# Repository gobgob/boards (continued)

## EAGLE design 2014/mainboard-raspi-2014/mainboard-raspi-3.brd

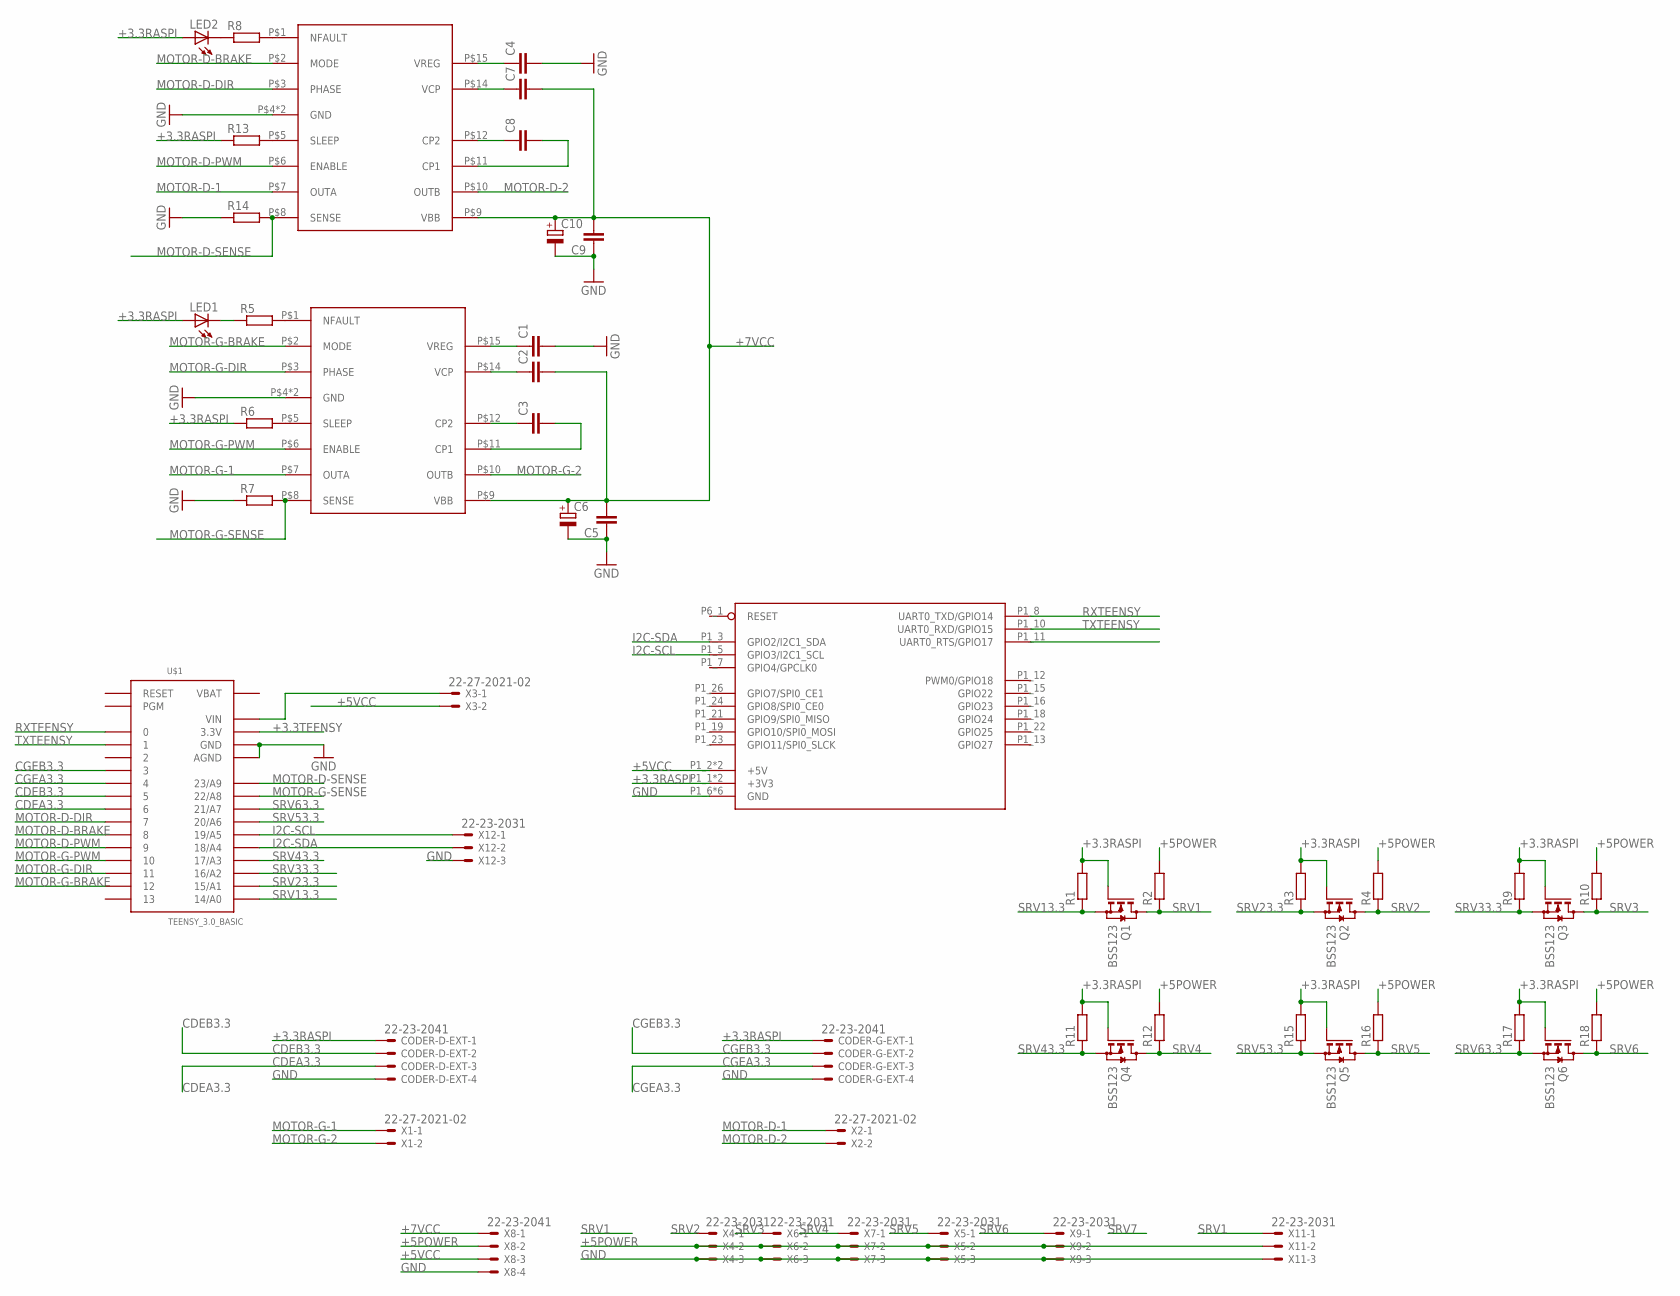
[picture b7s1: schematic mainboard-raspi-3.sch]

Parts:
C1, C2, C3, C4, C5, C7, C8, C9: C-EUC0805K; C0805K
C6, C10: CPOL-EUE3.5-8; E3,5-8
CODER-D-EXT: 22-23-2041
CODER-G-EXT: 22-23-2041
LED1, LED2: LED3MM
Q1, Q2, Q3, Q4, Q5, Q6: BSS123; SOT23
R1, R2, R3, R4, R9, R10, R11, R12, R15, R16, R17, R18: R-EU_R0603; R0603
R5, R8: R-EU_0204/7; 0204/7
R6, R7, R13, R14: R-EU_0204/5; 0204/5
U$1: TEENSY_3.0_BASIC
U$2: RPI-B-V2SHIELD; RPI-B-V2-SHIELD
U$3, U$4: A3950-DIL; DIL16
X1, X2, X3: 22-27-2021-02; 6410-02
X4, X5, X6, X7, X9, X11, X12: 22-23-2031
X8: 22-23-2041

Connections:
+3.3RASPI: CODER-D-EXT.1, CODER-G-EXT.1, LED1.A, LED2.A, Q1.1 (G), Q2.1 (G), Q3.1 (G), Q4.1 (G), Q5.1 (G), Q6.1 (G), R1.2, R3.2, R6.1, R9.2, R11.2, R13.1, R15.2, R17.2, U$2.P1_1 (+3V3), U$2.P1_17 (+3V3)
+3.3TEENSY: U$1.3.3V, U$1.3.3V1 (3.3V)
+5POWER: R2.2, R4.2, R10.2, R12.2, R16.2, R18.2, X4.2, X5.2, X6.2, X7.2, X8.2, X9.2, X11.2
+5VCC: U$2.P1_2 (+5V), U$2.P1_4 (+5V), X3.2, X8.3
+7VCC: C2.2, C5.2, C6.+, C7.2, C9.2, C10.+, U$3.P$9 (VBB), U$4.P$9 (VBB), X8.1
CDEA3.3: CODER-D-EXT.3, U$1.6
CDEB3.3: CODER-D-EXT.2, U$1.5
CGEA3.3: CODER-G-EXT.3, U$1.4
CGEB3.3: CODER-G-EXT.2, U$1.3
GND: C1.2, C4.2, C5.1, C6.-, C9.1, C10.-, CODER-D-EXT.4, CODER-G-EXT.4, R7.1, R14.1, U$1.AGND, U$1.GND, U$1.GND1 (GND), U$2.P1_6 (GND), U$2.P1_9 (GND), U$2.P1_14 (GND), U$2.P1_20 (GND), U$2.P1_25 (GND), U$2.P6_2 (GND), U$3.P$4 (GND), U$3.P$13 (GND), U$4.P$4 (GND), U$4.P$13 (GND), X4.3, X5.3, X6.3, X7.3, X8.4, X9.3, X11.3, X12.3
I2C-SCL: U$1.19/A5, U$2.P1_5 (GPIO3/I2C1_SCL), X12.1
I2C-SDA: U$1.18/A4, U$2.P1_3 (GPIO2/I2C1_SDA), X12.2
MOTOR-D-1: U$4.P$7 (OUTA), X2.1
MOTOR-D-2: U$4.P$10 (OUTB), X2.2
MOTOR-D-BRAKE: U$1.8, U$4.P$2 (MODE)
MOTOR-D-DIR: U$1.7, U$4.P$3 (PHASE)
MOTOR-D-PWM: U$1.9, U$4.P$6 (ENABLE)
MOTOR-D-SENSE: R14.2, U$1.23/A9, U$4.P$8 (SENSE)
MOTOR-G-1: U$3.P$7 (OUTA), X1.1
MOTOR-G-2: U$3.P$10 (OUTB), X1.2
MOTOR-G-BRAKE: U$1.12, U$3.P$2 (MODE)
MOTOR-G-DIR: U$1.11, U$3.P$3 (PHASE)
MOTOR-G-PWM: U$1.10, U$3.P$6 (ENABLE)
MOTOR-G-SENSE: R7.2, U$1.22/A8, U$3.P$8 (SENSE)
unnamed: U$1.VIN, X3.1
unnamed: R5.2, U$3.P$1 (NFAULT)
unnamed: R6.2, U$3.P$5 (SLEEP)
unnamed: R8.2, U$4.P$1 (NFAULT)
unnamed: C1.1, U$3.P$15 (VREG)
unnamed: C2.1, U$3.P$14 (VCP)
unnamed: C3.1, U$3.P$12 (CP2)
unnamed: LED1.K (C), R5.1
unnamed: R13.2, U$4.P$5 (SLEEP)
unnamed: C4.1, U$4.P$15 (VREG)
unnamed: C7.1, U$4.P$14 (VCP)
unnamed: C3.2, U$3.P$11 (CP1)
unnamed: C8.1, U$4.P$12 (CP2)
unnamed: C8.2, U$4.P$11 (CP1)
unnamed: LED2.K (C), R8.1
RESET: U$2.P6_1 (RESET)
RXTEENSY: U$1.0, U$2.P1_8 (UART0_TXD/GPIO14)
SRV1: Q1.3 (D), R2.1, X11.1
SRV2: Q2.3 (D), R4.1, X4.1
SRV3: Q3.3 (D), R10.1, X6.1
SRV4: Q4.3 (D), R12.1, X7.1
SRV5: Q5.3 (D), R16.1, X5.1
SRV6: Q6.3 (D), R18.1, X9.1
SRV13.3: Q1.2 (S), R1.1, U$1.14/A0
SRV23.3: Q2.2 (S), R3.1, U$1.15/A1
SRV33.3: Q3.2 (S), R9.1, U$1.16/A2
SRV43.3: Q4.2 (S), R11.1, U$1.17/A3
SRV53.3: Q5.2 (S), R15.1, U$1.20/A6
SRV63.3: Q6.2 (S), R17.1, U$1.21/A7
TXTEENSY: U$1.1, U$2.P1_10 (UART0_RXD/GPIO15)
VBAT: U$1.VBAT

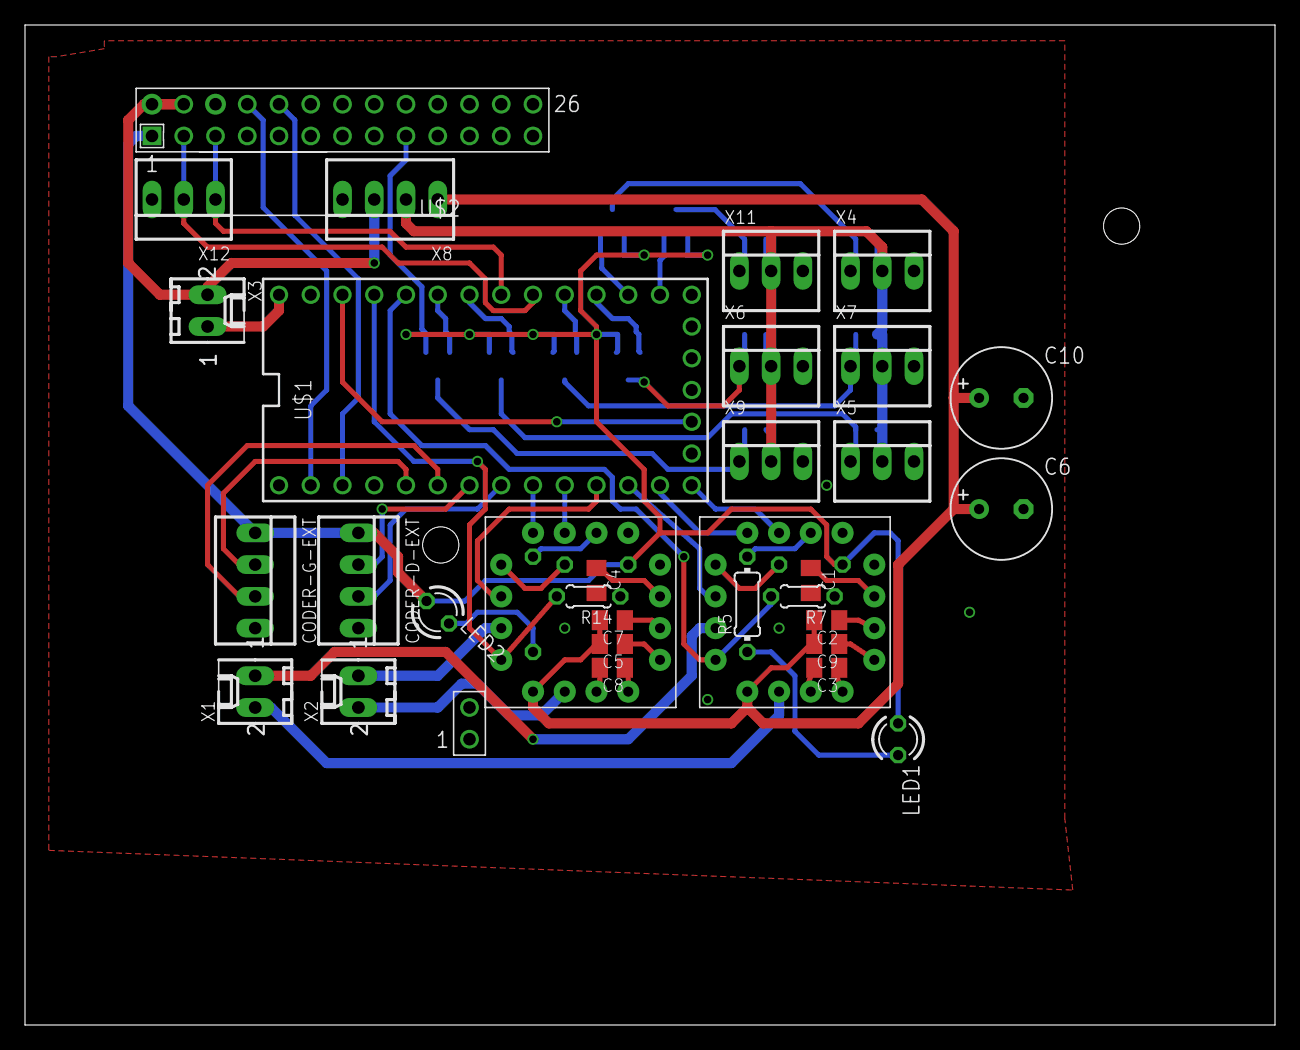
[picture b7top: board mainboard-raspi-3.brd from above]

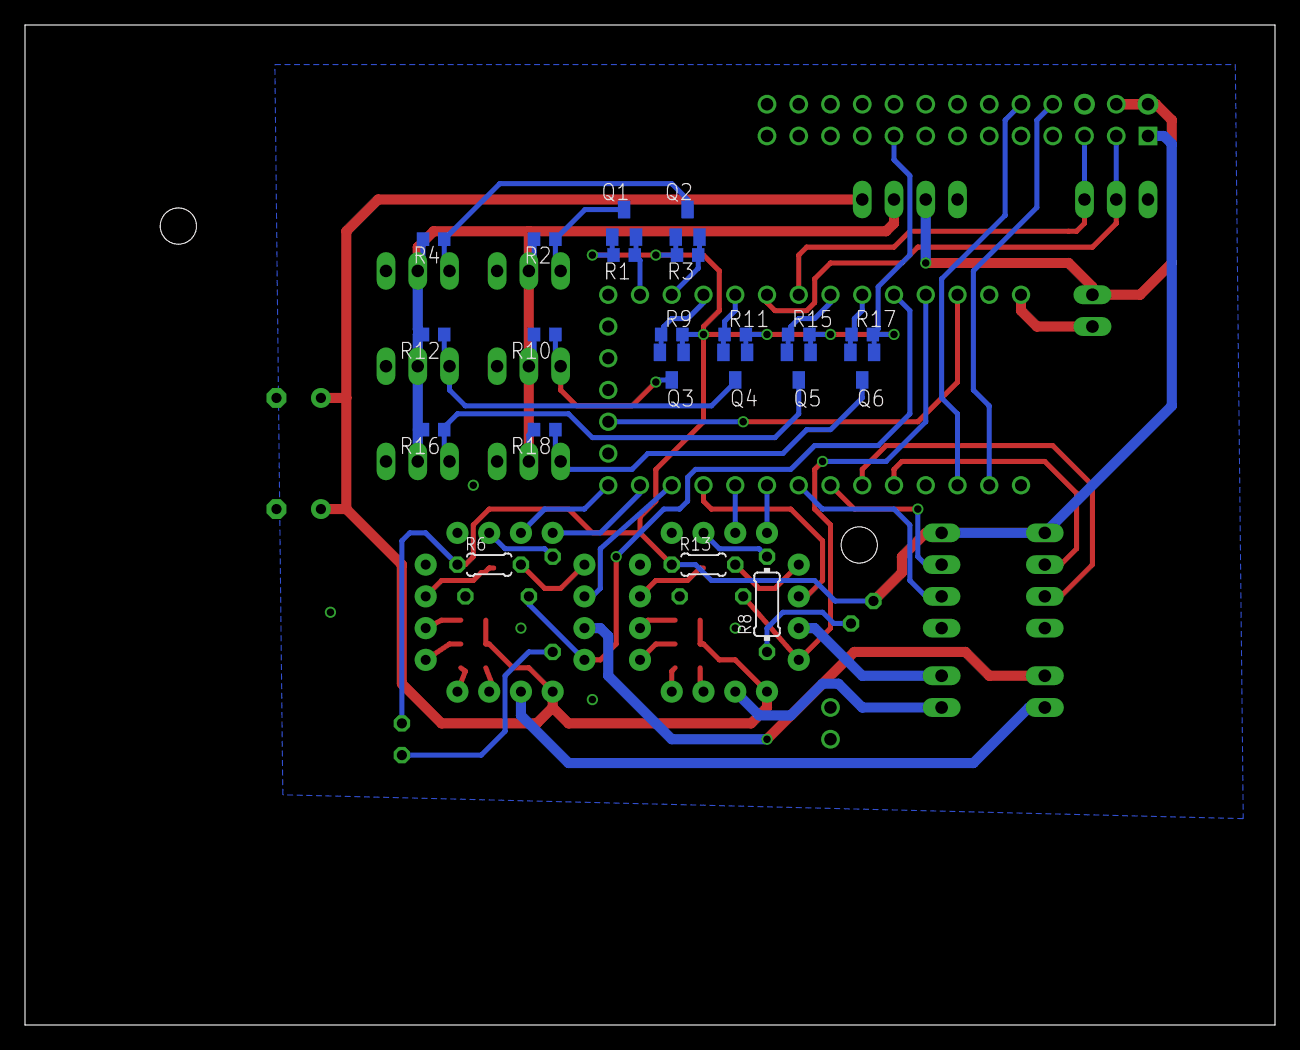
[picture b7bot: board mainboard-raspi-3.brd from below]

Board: 2 copper layers, 100.0 x 80.0 mm, 53 parts (21 on the bottom side), 53 nets.
